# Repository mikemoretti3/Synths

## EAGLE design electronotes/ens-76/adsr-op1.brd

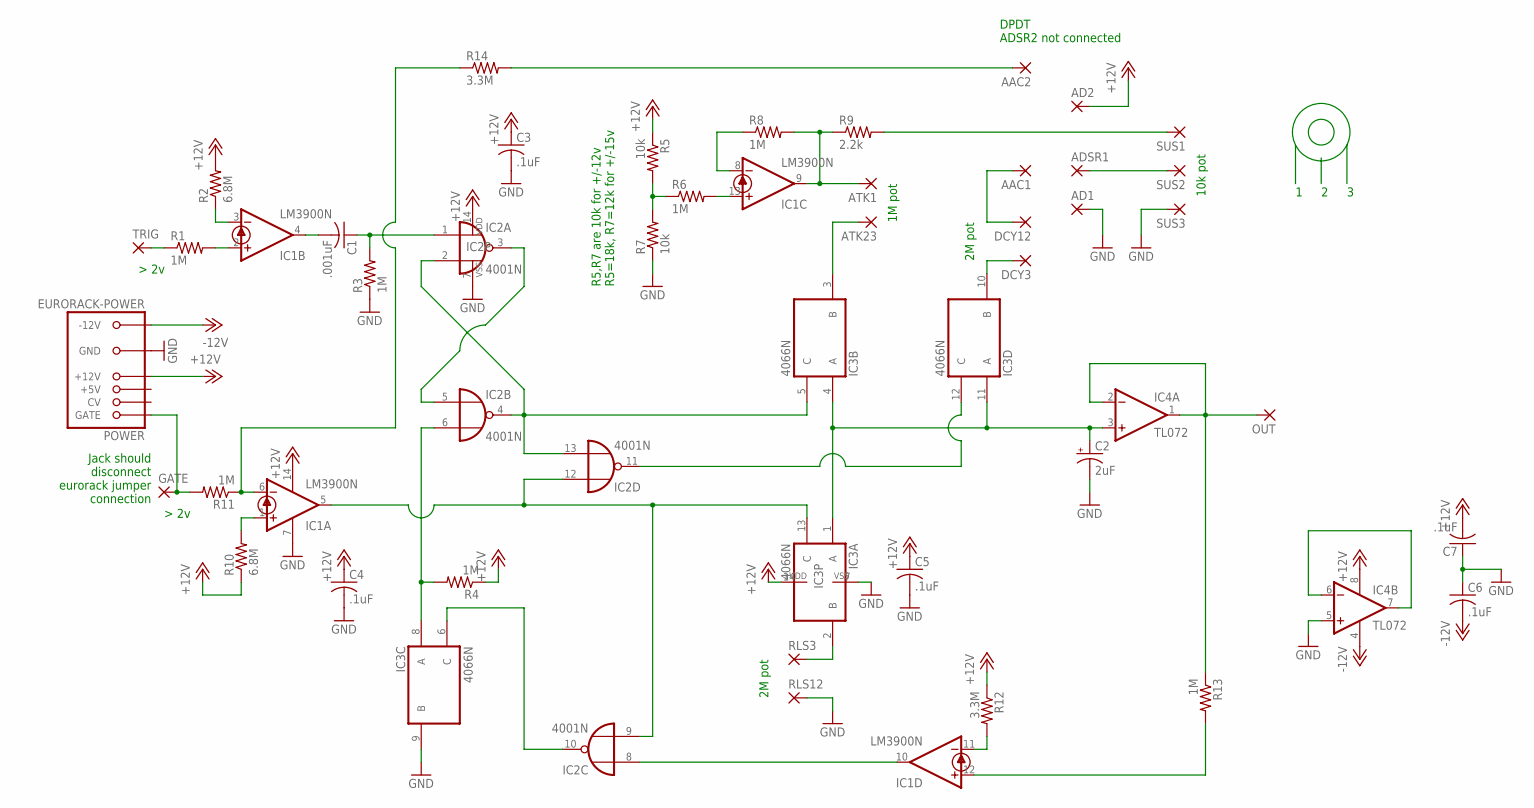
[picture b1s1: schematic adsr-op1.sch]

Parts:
AAC1, AAC2: 2,54/1,0
AD1, AD2: 2,54/1,0
ADSR1: 2,54/1,0
ATK1, ATK23: 2,54/1,0
C1: .001uF; C050-025X075
C2: 2uF; E2,5-5
C3, C4, C5, C6, C7: .1uF; C050-025X075
DCY3, DCY12: 2,54/1,0
GATE: 2,54/1,0
IC1: LM3900N; DIL14
IC2: 4001N; DIL14
IC3: 4066N; DIL14
IC4: TL072; DIL08
OUT: 2,54/1,0
POWER: EURORACK-POWER; PINSHRD_PTH_2X8
R1, R3, R4, R6, R8, R11, R13: 1M; 0207/10
R2, R10: 6.8M; 0207/10
R5, R7: 10k; 0207/10
R9: 2.2k; 0207/10
R12, R14: 3.3M; 0207/10
RLS3, RLS12: 2,54/1,0
SUS1, SUS2, SUS3: 2,54/1,0
TRIG: 2,54/1,0

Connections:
+12V: AD2.1, C3.1, C4.1, C5.1, C7.2, IC1.14 (V+), IC2.14 (VDD), IC3.14 (VDD), IC4.8 (V+), POWER.+12V@1 (+12V), POWER.+12V@2 (+12V), R2.2, R4.1, R5.1, R10.1, R12.1
-12V: C6.2, IC4.4 (V-), POWER.-12V@1 (-12V), POWER.-12V@2 (-12V)
GND: AD1.1, C2.-, C3.2, C4.2, C5.2, C6.1, C7.1, IC1.7 (GND), IC2.7 (VSS), IC3.7 (VSS), IC3.9 (B), IC4.5 (+IN), POWER.GND@1 (GND), POWER.GND@2 (GND), POWER.GND@3 (GND), POWER.GND@4 (GND), POWER.GND@5 (GND), POWER.GND@6 (GND), R3.1, R7.1, RLS12.1, SUS3.1
unnamed: IC4.6 (-IN), IC4.7 (OUT)
unnamed: IC1.3 (-IN), R2.1
unnamed: IC1.2 (+IN), R1.2
unnamed: R1.1, TRIG.1
unnamed: C1.2, IC1.4 (OUT)
unnamed: C1.1, IC2.1 (I0), R3.2
unnamed: IC2.2 (I1), IC2.4 (O), IC2.13 (I1), IC3.5 (C)
unnamed: IC2.3 (O), IC2.5 (I0)
unnamed: IC1.6 (-IN), R11.1, R14.1
unnamed: IC1.1 (+IN), R10.2
unnamed: IC2.10 (O), IC3.6 (C)
unnamed: GATE.1, POWER.GATE@1 (GATE), POWER.GATE@2 (GATE), R11.2
unnamed: IC2.6 (I1), IC3.8 (A), R4.2
unnamed: IC1.5 (OUT), IC2.9 (I1), IC2.12 (I0), IC3.13 (C)
unnamed: IC1.10 (OUT), IC2.8 (I0)
unnamed: IC3.2 (B), RLS3.1
unnamed: IC1.11 (-IN), R12.2
unnamed: C2.+, IC3.1 (A), IC3.4 (A), IC3.11 (A), IC4.3 (+IN)
unnamed: ATK23.1, IC3.3 (B)
unnamed: ATK1.1, IC1.9 (OUT), R8.2, R9.1
unnamed: IC1.13 (+IN), R6.2
unnamed: R5.2, R6.1, R7.2
unnamed: IC1.8 (-IN), R8.1
unnamed: IC2.11 (O), IC3.12 (C)
unnamed: DCY3.1, IC3.10 (B)
unnamed: AAC1.1, DCY12.1
unnamed: ADSR1.1, SUS2.1
unnamed: R9.2, SUS1.1
unnamed: AAC2.1, R14.2
unnamed: IC4.1 (OUT), IC4.2 (-IN), OUT.1, R13.1
unnamed: IC1.12 (+IN), R13.2

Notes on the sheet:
2M pot
1M pot
10k pot
DPDT ADSR2 not connected
R5,R7 are 10k for +/-12v R5=18k, R7=12k for +/-15v
Jack should disconnect eurorack jumper connection

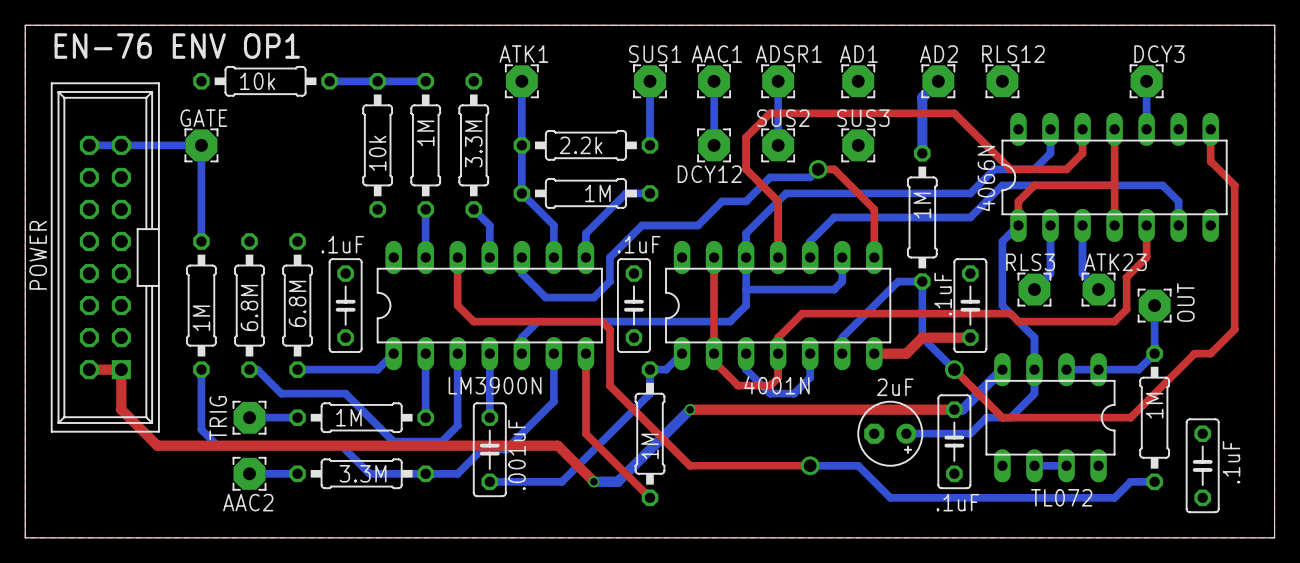
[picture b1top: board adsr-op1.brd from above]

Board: 2 copper layers, 99.1 x 40.6 mm, 43 parts (0 on the bottom side), 34 nets.

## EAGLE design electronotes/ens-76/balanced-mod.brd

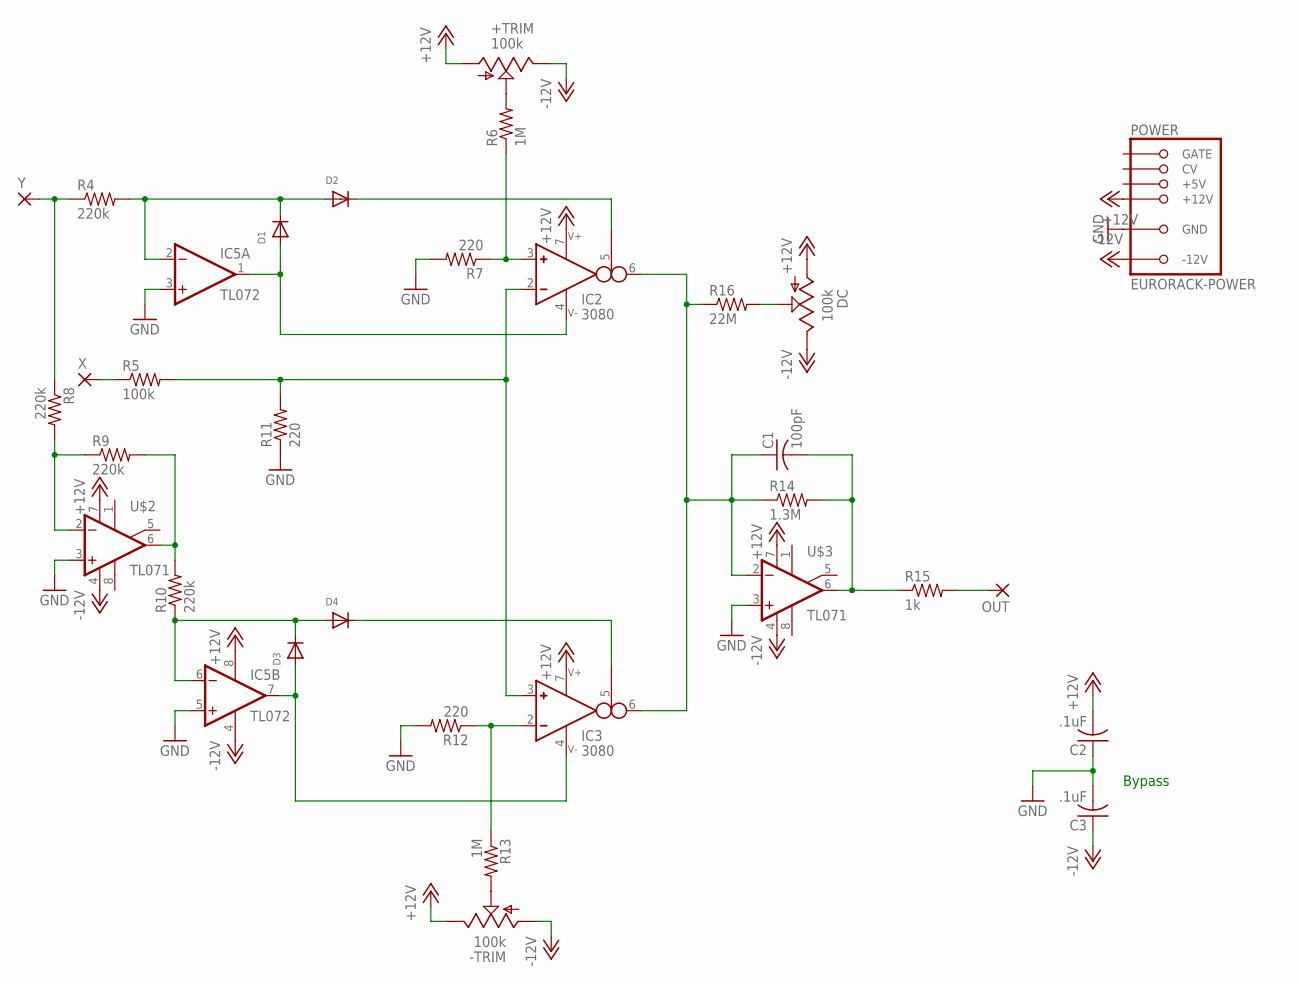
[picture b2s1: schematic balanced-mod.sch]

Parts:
+TRIM: 100k; RJ9W
-TRIM: 100k; RJ9W
C1: 100pF; C050-025X075
C2, C3: .1uF; C050-025X075
D1, D2, D3, D4: DIODEDO-1N4148; DO-1N4148
DC: 100k; RJ9W
IC2, IC3: 3080; DIL08
IC5: TL072; DIL08
OUT: 2,54/1,0
POWER: EURORACK-POWER; PINSHRD_PTH_2X8
R4, R8, R9, R10: 220k; 0207/10
R5: 100k; 0207/10
R6, R13: 1M; 0207/10
R7, R11, R12: 220; 0207/10
R14: 1.3M; 0207/10
R15: 1k; 0207/10
R16: 22M; 0207/10
U$2, U$3: TL071; DIL08
X: 2,54/1,0
Y: 2,54/1,0

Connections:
+12V: +TRIM.A, -TRIM.E, C2.2, DC.A, IC2.7, IC3.7, IC5.8 (V+), POWER.+12V@1 (+12V), POWER.+12V@2 (+12V), U$2.7 (V+), U$3.7 (V+)
-12V: +TRIM.E, -TRIM.A, C3.1, DC.E, IC5.4 (V-), POWER.-12V@1 (-12V), POWER.-12V@2 (-12V), U$2.4 (V-), U$3.4 (V-)
GND: C2.1, C3.2, IC5.3 (+IN), IC5.5 (+IN), POWER.GND@1 (GND), POWER.GND@2 (GND), POWER.GND@3 (GND), POWER.GND@4 (GND), POWER.GND@5 (GND), POWER.GND@6 (GND), R7.2, R11.1, R12.2, U$2.3 (+IN), U$3.3 (+IN)
unnamed: D1.C, D2.A, IC5.2 (-IN), R4.2
unnamed: R4.1, R8.1, Y.1
unnamed: R5.1, X.1
unnamed: +TRIM.S, R6.2
unnamed: IC2.3 (IN_P), R6.1, R7.1
unnamed: D2.C, IC2.5 (I_BIAS)
unnamed: IC2.2 (IN_N), IC3.3 (IN_P), R5.2, R11.2
unnamed: R8.2, R9.1, U$2.2 (-IN)
unnamed: C1.1, IC2.6 (OUT), IC3.6 (OUT), R14.1, R16.1, U$3.2 (-IN)
unnamed: DC.S, R16.2
unnamed: C1.2, R14.2, R15.1, U$3.6 (OUT)
unnamed: OUT.1, R15.2
unnamed: R9.2, R10.2, U$2.6 (OUT)
unnamed: D3.C, D4.A, IC5.6 (-IN), R10.1
unnamed: D3.A, IC3.4, IC5.7 (OUT)
unnamed: D4.C, IC3.5 (I_BIAS)
unnamed: IC3.2 (IN_N), R12.1, R13.1
unnamed: -TRIM.S, R13.2
V-: D1.A, IC2.4, IC5.1 (OUT)

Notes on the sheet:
Bypass

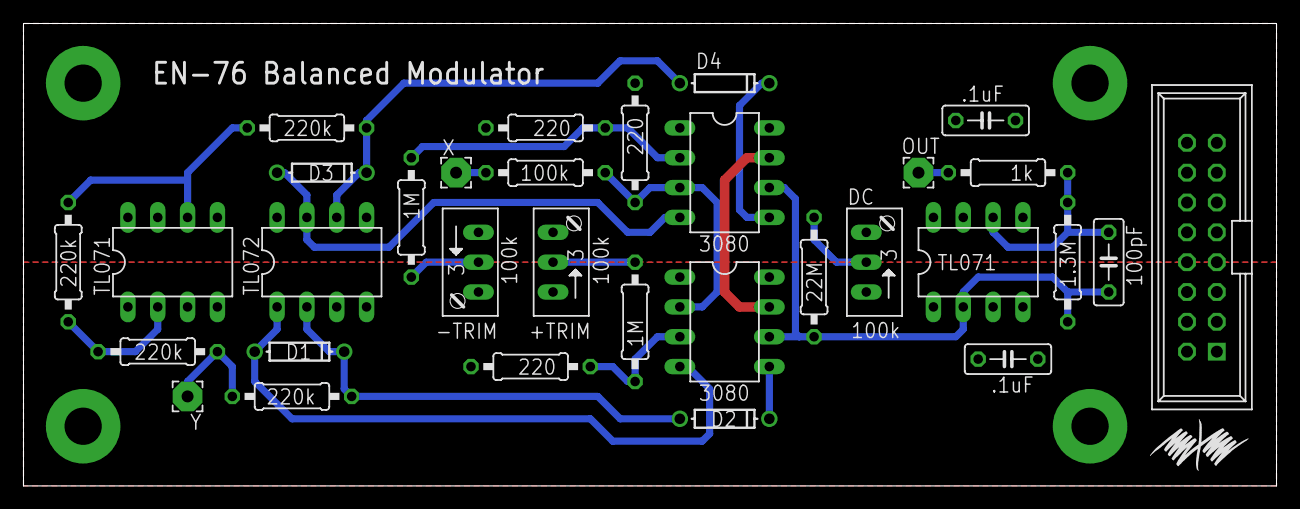
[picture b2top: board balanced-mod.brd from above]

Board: 2 copper layers, 106.7 x 39.4 mm, 32 parts (0 on the bottom side), 22 nets.

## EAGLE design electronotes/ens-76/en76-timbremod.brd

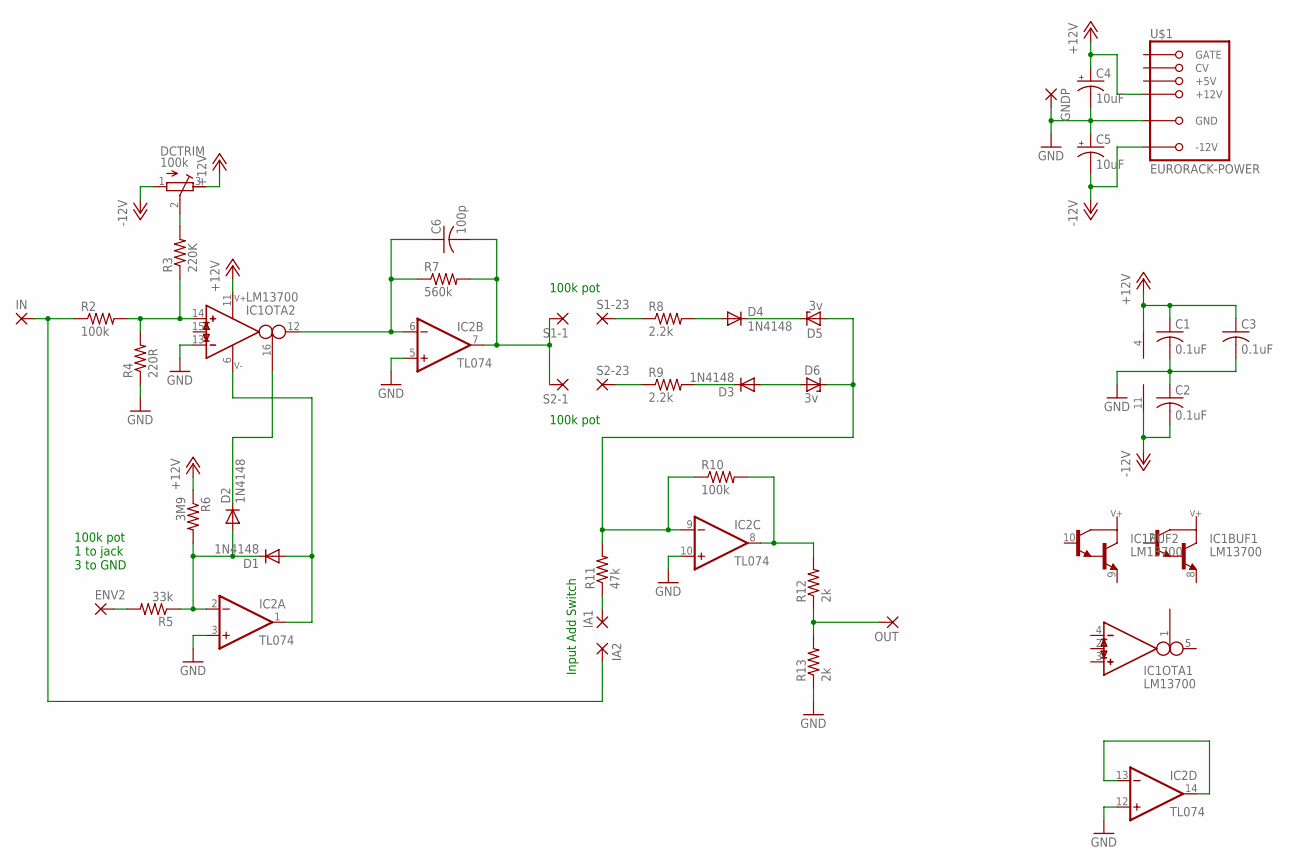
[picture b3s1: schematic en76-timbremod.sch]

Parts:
C1, C2, C3: 0.1uF; C050-025X075
C4, C5: 10uF; E2,5-5
C6: 100p; C050-025X075
D1, D2, D3, D4: 1N4148; DO35-7
D5, D6: 3v; DO35Z10
DCTRIM: 100k; RTRIM64W
ENV2: 2,54/1,0
GNDP: 2,54/1,0
IA1, IA2: 2,54/1,0
IC1: LM13700; DIL16
IC2: TL074; DIL14
IN: 2,54/1,0
OUT: 2,54/1,0
R2, R10: 100k; 0207/10
R3: 220K; 0207/10
R4: 220R; 0207/10
R5: 33k; 0207/10
R6: 3M9; 0207/10
R7: 560k; 0207/10
R8, R9: 2.2k; 0207/10
R11: 47k; 0207/10
R12, R13: 2k; 0207/10
S1-1, S1-23, S2-1, S2-23: 2,54/1,0
U$1: EURORACK-POWER; PINSHRD_PTH_2X8

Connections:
+12V: C1.1, C3.1, C4.+, DCTRIM.3 (E), IC1.11 (7), IC2.4 (V+), R6.1, U$1.+12V@1 (+12V), U$1.+12V@2 (+12V)
-12V: C2.2, C5.-, DCTRIM.1 (A), IC2.11 (V-), U$1.-12V@1 (-12V), U$1.-12V@2 (-12V)
GND: C1.2, C2.1, C3.2, C4.-, C5.+, GNDP.1, IC1.13 (IN_N), IC2.3 (+IN), IC2.5 (+IN), IC2.10 (+IN), IC2.12 (+IN), R4.1, R13.1, U$1.GND@1 (GND), U$1.GND@2 (GND), U$1.GND@3 (GND), U$1.GND@4 (GND), U$1.GND@5 (GND), U$1.GND@6 (GND)
unnamed: IA2.1, IN.1, R2.1
unnamed: IC1.14 (IN_P), R2.2, R3.1, R4.2
unnamed: DCTRIM.2 (S), R3.2
unnamed: ENV2.1, R5.2
unnamed: D1.C, D2.A, IC2.2 (-IN), R5.1, R6.2
unnamed: D1.A, IC1.6 (4), IC2.1 (OUT)
unnamed: D2.C, IC1.16 (I_BIAS)
unnamed: C6.1, IC1.12 (OUT), IC2.6 (-IN), R7.1
unnamed: C6.2, IC2.7 (OUT), R7.2, S1-1.1, S2-1.1
unnamed: D4.A, R8.2
unnamed: D3.C, R9.2
unnamed: D4.C, D5.C
unnamed: D3.A, D6.A
unnamed: R8.1, S1-23.1
unnamed: D5.A, D6.C, IC2.9 (-IN), R10.1, R11.2
unnamed: R9.1, S2-23.1
unnamed: IA1.1, R11.1
unnamed: IC2.8 (OUT), R10.2, R12.2
unnamed: OUT.1, R12.1, R13.2
unnamed: IC2.13 (-IN), IC2.14 (OUT)

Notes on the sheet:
100k pot 1 to jack 3 to GND
100k pot
Input Add Switch

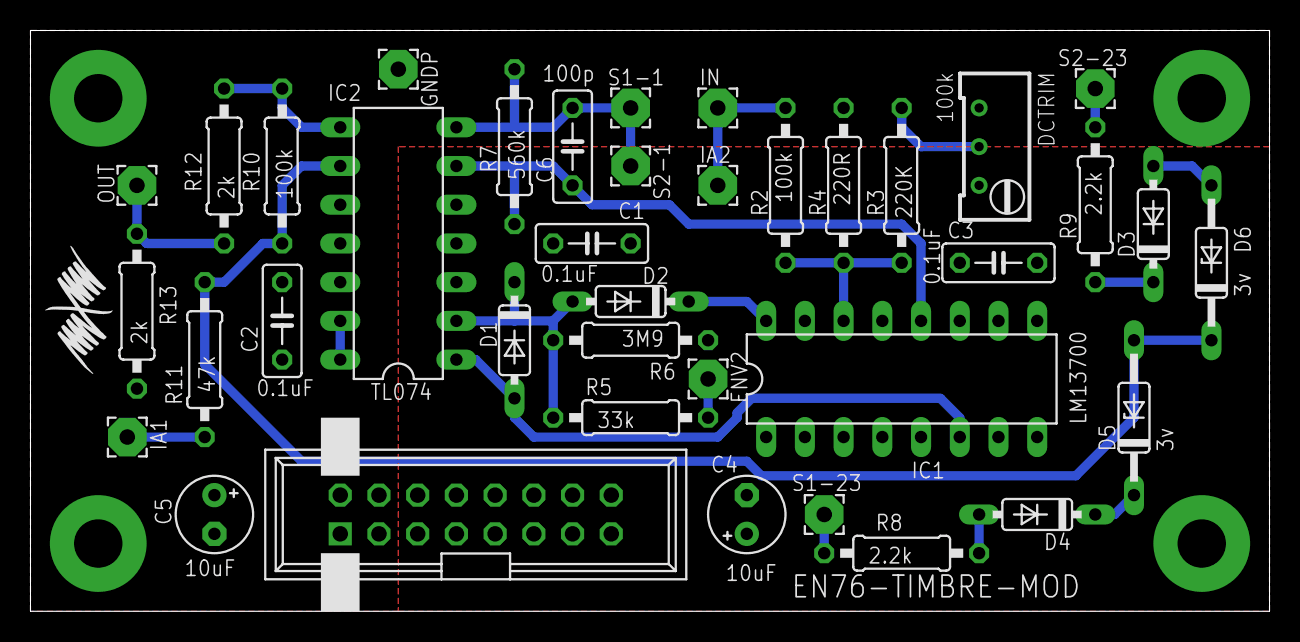
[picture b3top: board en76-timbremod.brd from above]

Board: 2 copper layers, 81.3 x 38.1 mm, 38 parts (0 on the bottom side), 23 nets.

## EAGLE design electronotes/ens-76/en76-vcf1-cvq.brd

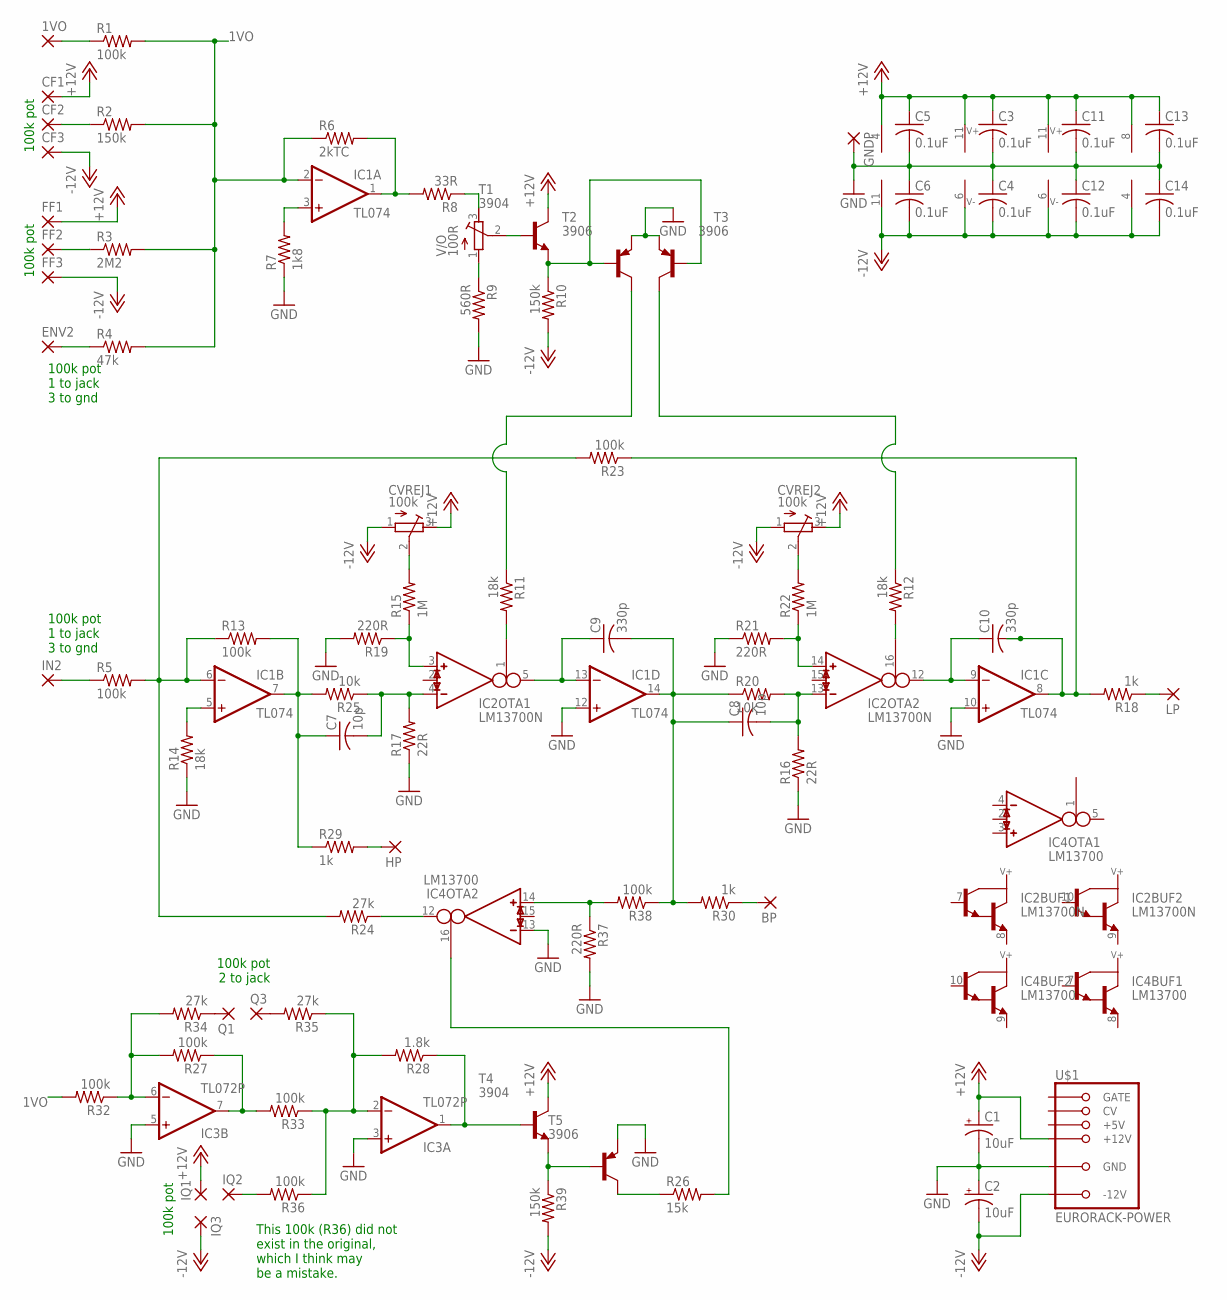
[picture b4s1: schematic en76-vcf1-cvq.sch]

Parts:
1VO: 2,54/1,0
BP: 2,54/1,0
C1, C2: 10uF; E2,5-5
C3, C4, C5, C6, C11, C12, C13, C14: 0.1uF; C050-025X075
C7, C8: 10p; C050-025X075
C9, C10: 330p; C050-025X075
CF1, CF2, CF3: 2,54/1,0
CVREJ1, CVREJ2: 100k; RTRIM64W
ENV2: 2,54/1,0
FF1, FF2, FF3: 2,54/1,0
GNDP: 2,54/1,0
HP: 2,54/1,0
IC1: TL074; DIL14
IC2: LM13700N; DIL16
IC3: TL072P; DIL08
IC4: LM13700; DIL16
IN2: 2,54/1,0
IQ1, IQ2, IQ3: 2,54/1,0
LP: 2,54/1,0
Q1, Q3: 2,54/1,0
R1, R5, R13, R23, R27, R32, R33, R36, R38: 100k; 0207/10
R2, R10, R39: 150k; 0207/10
R3: 2M2; 0207/10
R4: 47k; 0207/10
R6: 2kTC; 0207/10
R7: 1k8; 0207/10
R8: 33R; 0207/10
R9: 560R; 0207/10
R11, R12, R14: 18k; 0207/10
R15, R22: 1M; 0207/10
R16, R17: 22R; 0207/10
R18, R29, R30: 1k; 0207/10
R19, R21, R37: 220R; 0207/10
R20, R25: 10k; 0207/10
R24, R34, R35: 27k; 0207/10
R26: 15k; 0207/10
R28: 1.8k; 0207/10
T1, T4: 3904; TO92-EBC
T2, T3, T5: 3906; TO92-EBC
U$1: EURORACK-POWER; PINSHRD_PTH_2X8
V/O: 100R; RTRIM64W

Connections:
1VO: IC1.2 (-IN), R1.2, R2.2, R3.2, R4.2, R6.1, R32.2
+12V: C1.+, C3.1, C5.1, C11.1, C13.1, CF1.1, CVREJ1.3 (E), CVREJ2.3 (E), FF1.1, IC1.4 (V+), IC2.11 (7), IC3.8 (V+), IC4.11 (7), IQ1.1, T1.C, T4.C, U$1.+12V@1 (+12V), U$1.+12V@2 (+12V)
-12V: C2.-, C4.2, C6.2, C12.2, C14.2, CF3.1, CVREJ1.1 (A), CVREJ2.1 (A), FF3.1, IC1.11 (V-), IC2.6 (4), IC3.4 (V-), IC4.6 (4), IQ3.1, R10.2, R39.2, U$1.-12V@1 (-12V), U$1.-12V@2 (-12V)
GND: C1.-, C2.+, C3.2, C4.1, C5.2, C6.1, C11.2, C12.1, C13.2, C14.1, GNDP.1, IC1.10 (+IN), IC1.12 (+IN), IC3.3 (+IN), IC3.5 (+IN), IC4.13 (IN_N), R7.1, R9.2, R14.1, R16.1, R17.1, R19.2, R21.1, R37.2, T2.E, T3.E, T5.E, U$1.GND@1 (GND), U$1.GND@2 (GND), U$1.GND@3 (GND), U$1.GND@4 (GND), U$1.GND@5 (GND), U$1.GND@6 (GND)
unnamed: 1VO.1, R1.1
unnamed: CF2.1, R2.1
unnamed: FF2.1, R3.1
unnamed: ENV2.1, R4.1
unnamed: IN2.1, R5.1
unnamed: IC1.6 (-IN), R5.2, R13.1, R23.2, R24.2
unnamed: C7.1, IC1.7 (OUT), R13.2, R25.2, R29.1
unnamed: IC1.5 (+IN), R14.2
unnamed: C9.1, IC1.13 (-IN), IC2.5 (OUT)
unnamed: C8.1, C9.2, IC1.14 (OUT), R20.1, R30.2, R38.1
unnamed: C10.1, IC1.9 (-IN), IC2.12 (OUT)
unnamed: C10.2, IC1.8 (OUT), R18.2, R23.1
unnamed: IC2.14 (IN_P), R21.2, R22.1
unnamed: CVREJ2.2 (S), R22.2
unnamed: C8.2, IC2.13 (IN_N), R16.2, R20.2
unnamed: IC3.7 (OUT), R27.1, R33.2
unnamed: IC1.1 (OUT), R6.2, R8.2
unnamed: IC1.3 (+IN), R7.2
unnamed: C7.2, IC2.4 (IN_N), R17.2, R25.1
unnamed: R9.1, V/O.1 (A)
unnamed: R8.1, V/O.3 (E)
unnamed: T1.B, V/O.2 (S)
unnamed: R10.1, T1.E, T2.B, T3.B
unnamed: IC2.3 (IN_P), R15.1, R19.1
unnamed: CVREJ1.2 (S), R15.2
unnamed: IC2.1 (I_BIAS), R11.2
unnamed: HP.1, R29.2
unnamed: IC2.16 (I_BIAS), R12.2
unnamed: LP.1, R18.1
unnamed: BP.1, R30.1
unnamed: IQ2.1, R36.2
unnamed: Q1.1, R34.1
unnamed: R12.1, T3.C
unnamed: R11.1, T2.C
unnamed: IC4.12 (OUT), R24.1
unnamed: R26.1, T5.C
unnamed: R39.1, T4.E, T5.B
unnamed: IC3.2 (-IN), R28.2, R33.1, R35.1, R36.1
unnamed: IC3.6 (-IN), R27.2, R32.1, R34.2
unnamed: IC3.1 (OUT), R28.1, T4.B
unnamed: Q3.1, R35.2
unnamed: IC4.14 (IN_P), R37.1, R38.2
unnamed: IC4.16 (I_BIAS), R26.2

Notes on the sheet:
100k pot 1 to jack 3 to gnd
100k pot
100k pot 2 to jack
This 100k (R36) did not exist in the original, which I think may be a mistake.

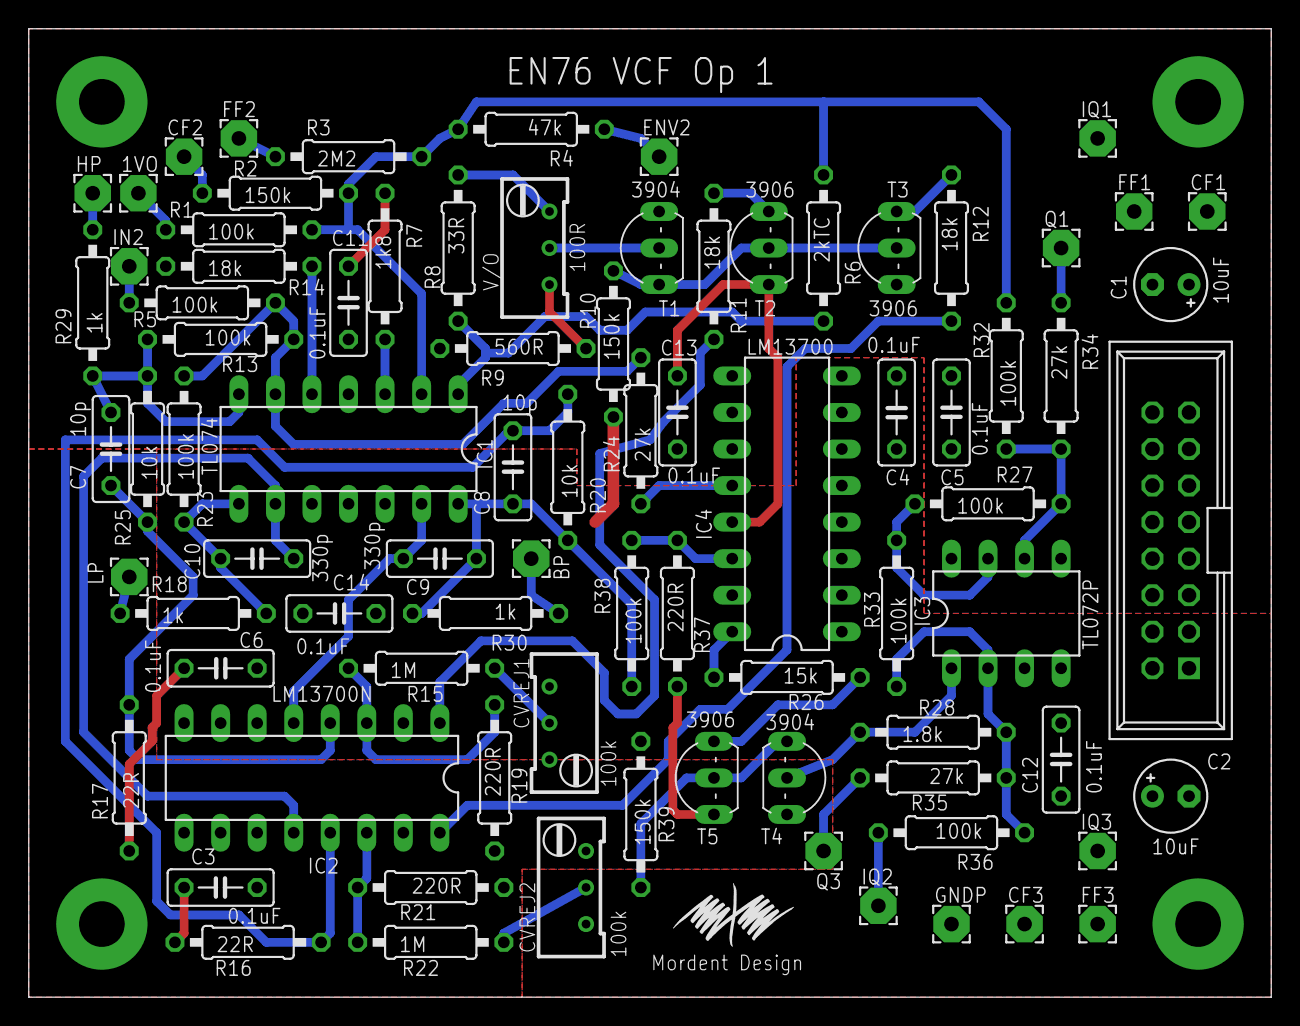
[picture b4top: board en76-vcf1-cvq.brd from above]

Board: 2 copper layers, 86.4 x 67.3 mm, 83 parts (0 on the bottom side), 47 nets.

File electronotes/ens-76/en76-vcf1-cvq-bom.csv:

"Part";"Value";"Device";"Package";"Description";"";
"1VO";"";"2,54/1,0";"2,54/1,0";"THROUGH-HOLE PAD";"";
"BP";"";"2,54/1,0";"2,54/1,0";"THROUGH-HOLE PAD";"";
"C1";"10uF";"CPOL-USE2.5-5";"E2,5-5";"POLARIZED CAPACITOR, American symbol";"";
"C2";"10uF";"CPOL-USE2.5-5";"E2,5-5";"POLARIZED CAPACITOR, American symbol";"";
"C3";"0.1uF";"C-US050-025X075";"C050-025X075";"CAPACITOR, American symbol";"";
"C4";"0.1uF";"C-US050-025X075";"C050-025X075";"CAPACITOR, American symbol";"";
"C5";"0.1uF";"C-US050-025X075";"C050-025X075";"CAPACITOR, American symbol";"";
"C6";"0.1uF";"C-US050-025X075";"C050-025X075";"CAPACITOR, American symbol";"";
"C7";"10p";"C-US050-025X075";"C050-025X075";"CAPACITOR, American symbol";"";
"C8";"10p";"C-US050-025X075";"C050-025X075";"CAPACITOR, American symbol";"";
"C9";"330p";"C-US050-025X075";"C050-025X075";"CAPACITOR, American symbol";"";
"C10";"330p";"C-US050-025X075";"C050-025X075";"CAPACITOR, American symbol";"";
"C11";"0.1uF";"C-US050-025X075";"C050-025X075";"CAPACITOR, American symbol";"";
"C12";"0.1uF";"C-US050-025X075";"C050-025X075";"CAPACITOR, American symbol";"";
"C13";"0.1uF";"C-US050-025X075";"C050-025X075";"CAPACITOR, American symbol";"";
"C14";"0.1uF";"C-US050-025X075";"C050-025X075";"CAPACITOR, American symbol";"";
"CF1";"";"2,54/1,0";"2,54/1,0";"THROUGH-HOLE PAD";"";
"CF2";"";"2,54/1,0";"2,54/1,0";"THROUGH-HOLE PAD";"";
"CF3";"";"2,54/1,0";"2,54/1,0";"THROUGH-HOLE PAD";"";
"CVREJ1";"100k";"R-TRIMM64W";"RTRIM64W";"Trimm resistor";"";
"CVREJ2";"100k";"R-TRIMM64W";"RTRIM64W";"Trimm resistor";"";
"ENV2";"";"2,54/1,0";"2,54/1,0";"THROUGH-HOLE PAD";"";
"FF1";"";"2,54/1,0";"2,54/1,0";"THROUGH-HOLE PAD";"";
"FF2";"";"2,54/1,0";"2,54/1,0";"THROUGH-HOLE PAD";"";
"FF3";"";"2,54/1,0";"2,54/1,0";"THROUGH-HOLE PAD";"";
"GNDP";"";"2,54/1,0";"2,54/1,0";"THROUGH-HOLE PAD";"";
"HP";"";"2,54/1,0";"2,54/1,0";"THROUGH-HOLE PAD";"";
"IC1";"TL074";"TL074-TOPP";"DIL14";"OP AMP";"";
"IC2";"LM13700N";"LM13700N";"DIL16";"Dual OTA with buffers";"";
"IC3";"TL072P";"TL072P";"DIL08";"OP AMP";"";
"IC4";"LM13700";"LM13700-TOPDIP16";"DIL16";"";"";
"IN2";"";"2,54/1,0";"2,54/1,0";"THROUGH-HOLE PAD";"";
"IQ1";"";"2,54/1,0";"2,54/1,0";"THROUGH-HOLE PAD";"";
"IQ2";"";"2,54/1,0";"2,54/1,0";"THROUGH-HOLE PAD";"";
"IQ3";"";"2,54/1,0";"2,54/1,0";"THROUGH-HOLE PAD";"";
"LP";"";"2,54/1,0";"2,54/1,0";"THROUGH-HOLE PAD";"";
"Q1";"";"2,54/1,0";"2,54/1,0";"THROUGH-HOLE PAD";"";
"Q3";"";"2,54/1,0";"2,54/1,0";"THROUGH-HOLE PAD";"";
"R1";"100k";"R-US_0207/10";"0207/10";"RESISTOR, American symbol";"";
"R2";"150k";"R-US_0207/10";"0207/10";"RESISTOR, American symbol";"";
"R3";"2M2";"R-US_0207/10";"0207/10";"RESISTOR, American symbol";"";
"R4";"47k";"R-US_0207/10";"0207/10";"RESISTOR, American symbol";"";
"R5";"100k";"R-US_0207/10";"0207/10";"RESISTOR, American symbol";"";
"R6";"2kTC";"R-US_0207/10";"0207/10";"RESISTOR, American symbol";"";
"R7";"1k8";"R-US_0207/10";"0207/10";"RESISTOR, American symbol";"";
"R8";"33R";"R-US_0207/10";"0207/10";"RESISTOR, American symbol";"";
"R9";"560R";"R-US_0207/10";"0207/10";"RESISTOR, American symbol";"";
"R10";"150k";"R-US_0207/10";"0207/10";"RESISTOR, American symbol";"";
"R11";"18k";"R-US_0207/10";"0207/10";"RESISTOR, American symbol";"";
"R12";"18k";"R-US_0207/10";"0207/10";"RESISTOR, American symbol";"";
"R13";"100k";"R-US_0207/10";"0207/10";"RESISTOR, American symbol";"";
"R14";"18k";"R-US_0207/10";"0207/10";"RESISTOR, American symbol";"";
"R15";"1M";"R-US_0207/10";"0207/10";"RESISTOR, American symbol";"";
"R16";"22R";"R-US_0207/10";"0207/10";"RESISTOR, American symbol";"";
"R17";"22R";"R-US_0207/10";"0207/10";"RESISTOR, American symbol";"";
"R18";"1k";"R-US_0207/10";"0207/10";"RESISTOR, American symbol";"";
"R19";"220R";"R-US_0207/10";"0207/10";"RESISTOR, American symbol";"";
"R20";"10k";"R-US_0207/10";"0207/10";"RESISTOR, American symbol";"";
"R21";"220R";"R-US_0207/10";"0207/10";"RESISTOR, American symbol";"";
"R22";"1M";"R-US_0207/10";"0207/10";"RESISTOR, American symbol";"";
"R23";"100k";"R-US_0207/10";"0207/10";"RESISTOR, American symbol";"";
"R24";"27k";"R-US_0207/10";"0207/10";"RESISTOR, American symbol";"";
"R25";"10k";"R-US_0207/10";"0207/10";"RESISTOR, American symbol";"";
"R26";"15k";"R-US_0207/10";"0207/10";"RESISTOR, American symbol";"";
"R27";"100k";"R-US_0207/10";"0207/10";"RESISTOR, American symbol";"";
"R28";"1.8k";"R-US_0207/10";"0207/10";"RESISTOR, American symbol";"";
"R29";"1k";"R-US_0207/10";"0207/10";"RESISTOR, American symbol";"";
"R30";"1k";"R-US_0207/10";"0207/10";"RESISTOR, American symbol";"";
"R32";"100k";"R-US_0207/10";"0207/10";"RESISTOR, American symbol";"";
"R33";"100k";"R-US_0207/10";"0207/10";"RESISTOR, American symbol";"";
"R34";"27k";"R-US_0207/10";"0207/10";"RESISTOR, American symbol";"";
"R35";"27k";"R-US_0207/10";"0207/10";"RESISTOR, American symbol";"";
"R36";"100k";"R-US_0207/10";"0207/10";"RESISTOR, American symbol";"";
"R37";"220R";"R-US_0207/10";"0207/10";"RESISTOR, American symbol";"";
"R38";"100k";"R-US_0207/10";"0207/10";"RESISTOR, American symbol";"";
"R39";"150k";"R-US_0207/10";"0207/10";"RESISTOR, American symbol";"";
"T1";"3904";"-NPN-TO92-EBC";"TO92-EBC";"NPN Transistror";"";
"T2";"3906";"-PNP-TO92-EBC";"TO92-EBC";"PNP Transistror";"";
"T3";"3906";"-PNP-TO92-EBC";"TO92-EBC";"PNP Transistror";"";
"T4";"3904";"-NPN-TO92-EBC";"TO92-EBC";"NPN Transistror";"";
"T5";"3906";"-PNP-TO92-EBC";"TO92-EBC";"PNP Transistror";"";
"U$1";"EURORACK-POWER";"EURORACK-POWER";"PINSHRD_PTH_2X8";"";"";
"V/O";"100R";"R-TRIMM64W";"RTRIM64W";"Trimm resistor";"";

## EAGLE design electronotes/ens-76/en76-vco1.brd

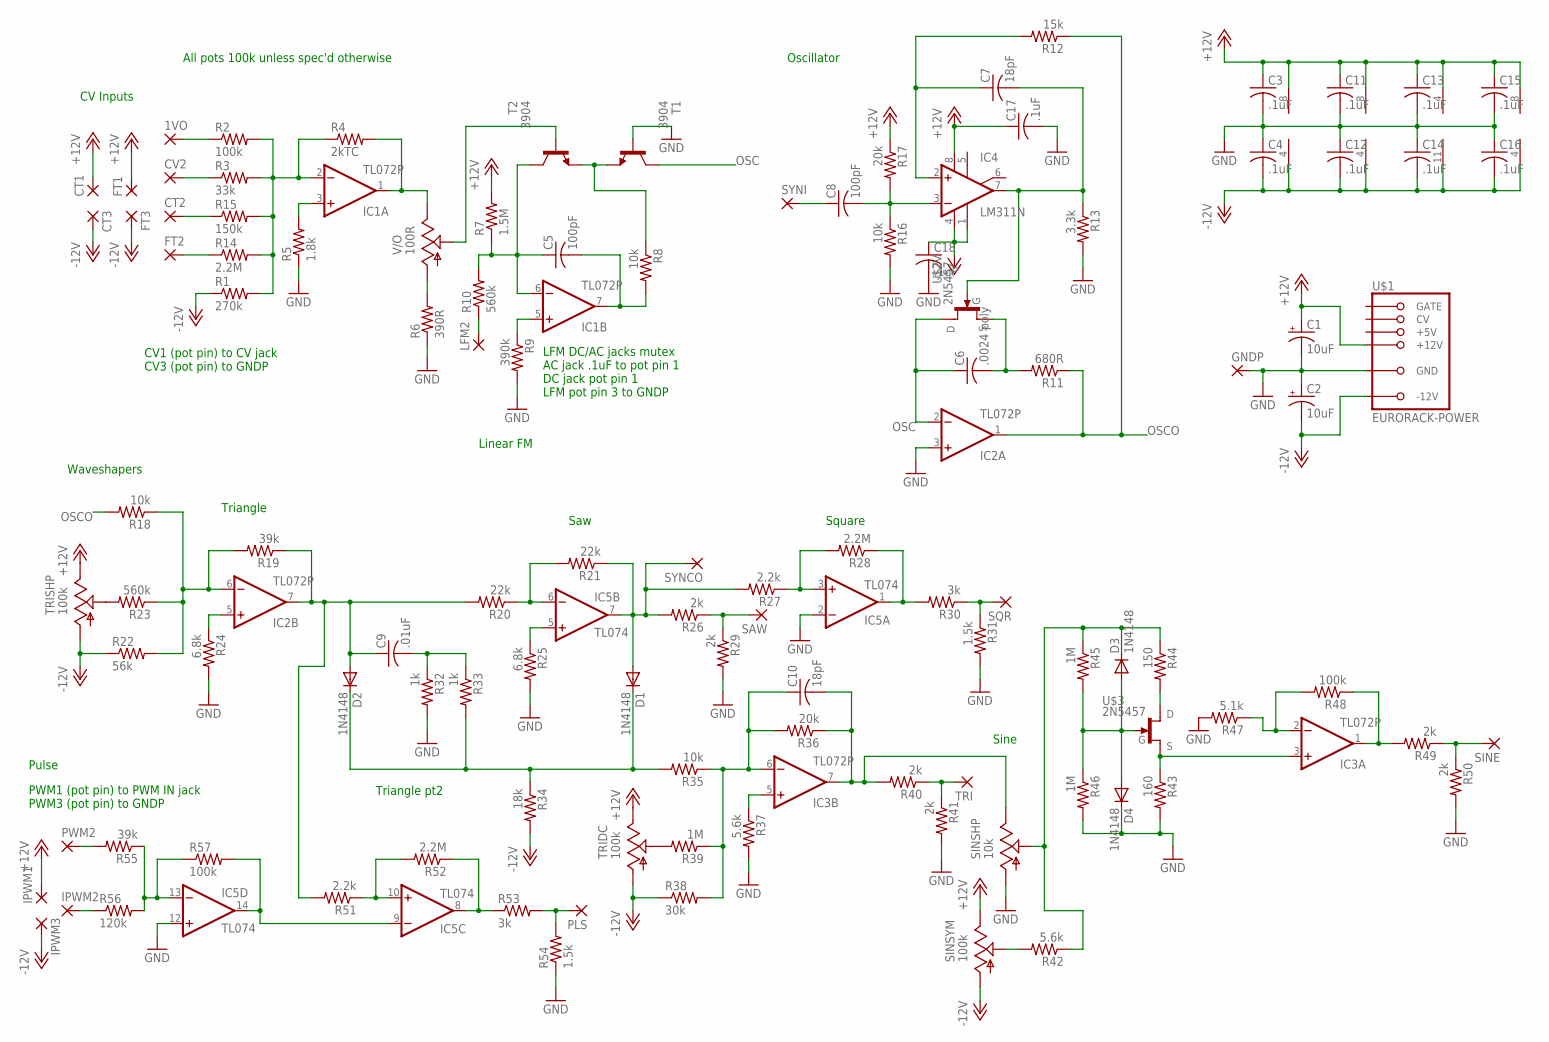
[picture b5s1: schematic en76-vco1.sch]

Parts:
1VO: 2,54/1,0
C1, C2: 10uF; E2-5
C3, C4, C11, C12, C13, C14, C15, C16, C17, C18: .1uF; C050-025X075
C5, C8: 100pF; C050-025X075
C6: .0024 poly; C050-025X075
C7, C10: 18pF; C050-025X075
C9: .01uF; C050-025X075
CT1, CT2, CT3: 2,54/1,0
CV2: 2,54/1,0
D1, D2, D3, D4: 1N4148; DO35-7
FT1, FT2, FT3: 2,54/1,0
GNDP: 2,54/1,0
IC1, IC2, IC3: TL072P; DIL08
IC4: LM311N; DIL08
IC5: TL074; DIL14
IPWM1, IPWM2, IPWM3: 2,54/1,0
LFM2: 2,54/1,0
PLS: 2,54/1,0
PWM2: 2,54/1,0
R1: 270k; 0207/10
R2, R48, R57: 100k; 0207/10
R3: 33k; 0207/10
R4: 2kTC; 0207/10
R5: 1.8k; 0207/10
R6: 390R; 0207/10
R7: 1.5M; 0207/10
R8, R16, R18, R35: 10k; 0207/10
R9: 390k; 0207/10
R10, R23: 560k; 0207/10
R11: 680R; 0207/10
R12: 15k; 0207/10
R13: 3.3k; 0207/10
R14, R28, R52: 2.2M; 0207/10
R15: 150k; 0207/10
R17, R36: 20k; 0207/10
R19, R55: 39k; 0207/10
R20, R21: 22k; 0207/10
R22: 56k; 0207/10
R24, R25: 6.8k; 0207/10
R26, R29, R40, R41, R49, R50: 2k; 0207/10
R27, R51: 2.2k; 0207/10
R30, R53: 3k; 0207/10
R31, R54: 1.5k; 0207/10
R32, R33: 1k; 0207/10
R34: 18k; 0207/10
R37, R42: 5.6k; 0207/10
R38: 30k; 0207/10
R39, R45, R46: 1M; 0207/10
R43: 160; 0207/10
R44: 150; 0207/10
R47: 5.1k; 0207/10
R56: 120k; 0207/10
SAW: 2,54/1,0
SINE: 2,54/1,0
SINSHP: 10k; RJ9W
SINSYM: 100k; RJ9W
SQR: 2,54/1,0
SYNCO: 2,54/1,0
SYNI: 2,54/1,0
T1, T2: 3904; TO92-EBC
TRI: 2,54/1,0
TRIDC: 100k; RJ9W
TRISHP: 100k; RJ9W
U$1: EURORACK-POWER; PINSHRD_PTH_2X8
U$2, U$3: 2N5457; TO-92
V/O: 100R; RJ9W

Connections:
+12V: C1.+, C3.1, C11.1, C13.1, C15.1, C17.1, CT1.1, FT1.1, IC1.8 (V+), IC2.8 (V+), IC3.8 (V+), IC4.8 (V+), IC5.4 (V+), IPWM1.1, R7.2, R17.1, SINSYM.E, TRIDC.E, TRISHP.E, U$1.+12V@1 (+12V), U$1.+12V@2 (+12V)
-12V: C2.-, C4.2, C12.2, C14.2, C16.2, C18.1, CT3.1, FT3.1, IC1.4 (V-), IC2.4 (V-), IC3.4 (V-), IC4.1 (GND), IC4.4 (V-), IC5.11 (V-), IPWM3.1, R1.1, R22.1, R34.2, R38.1, SINSYM.A, TRIDC.A, TRISHP.A, U$1.-12V@1 (-12V), U$1.-12V@2 (-12V)
GND: C1.-, C2.+, C3.2, C4.1, C11.2, C12.1, C13.2, C14.1, C15.2, C16.1, C17.2, C18.2, D4.C, GNDP.1, IC2.3 (+IN), IC5.2 (-IN), IC5.12 (+IN), R5.1, R6.1, R9.2, R13.2, R16.2, R24.2, R25.2, R29.2, R31.2, R32.2, R37.2, R41.2, R43.2, R46.2, R47.2, R50.2, R54.1, SINSHP.A, T1.B, U$1.GND@1 (GND), U$1.GND@2 (GND), U$1.GND@3 (GND), U$1.GND@4 (GND), U$1.GND@5 (GND), U$1.GND@6 (GND)
unnamed: CT2.1, R15.1
unnamed: CV2.1, R3.1
unnamed: 1VO.1, R2.1
unnamed: T2.B, V/O.S
unnamed: IC1.3 (+IN), R5.2
unnamed: IC1.2 (-IN), R1.2, R2.2, R3.2, R4.1, R14.2, R15.2
unnamed: IC1.1 (OUT), R4.2, V/O.E
unnamed: R6.2, V/O.A
unnamed: C5.1, IC1.6 (-IN), R7.1, R10.2, T2.C
unnamed: R8.1, T1.E, T2.E
unnamed: C5.2, IC1.7 (OUT), R8.2
unnamed: FT2.1, R14.1
unnamed: LFM2.1, R10.1
unnamed: IC1.5 (+IN), R9.1
unnamed: C7.1, IC4.2 (+IN), R12.2
unnamed: C7.2, IC4.7 (OUT), R13.1, U$2.3 (G)
unnamed: R23.2, TRISHP.S
unnamed: C6.2, R11.2, U$2.2 (S)
unnamed: D1.A, IC5.7 (OUT), R21.1, R26.2, R27.2, SYNCO.1
unnamed: C8.1, SYNI.1
unnamed: C8.2, IC4.3 (-IN), R16.1, R17.2
unnamed: PWM2.1, R55.2
unnamed: IC2.5 (+IN), R24.1
unnamed: IC2.6 (-IN), R18.1, R19.2, R22.2, R23.1
unnamed: R26.1, R29.1, SAW.1
unnamed: IC5.6 (-IN), R20.1, R21.2
unnamed: C9.2, R32.1, R33.1
unnamed: IC5.5 (+IN), R25.1
unnamed: IC5.3 (+IN), R27.1, R28.2
unnamed: IC5.1 (OUT), R28.1, R30.2
unnamed: R30.1, R31.1, SQR.1
unnamed: D1.C, D2.C, R33.2, R34.1, R35.2
unnamed: R40.1, R41.1, TRI.1
unnamed: C10.2, IC3.7 (OUT), R36.1, R40.2, SINSHP.E
unnamed: IC3.5 (+IN), R37.1
unnamed: R39.2, TRIDC.S
unnamed: C10.1, IC3.6 (-IN), R35.1, R36.2, R38.2, R39.1
unnamed: IC3.3 (+IN), R43.1, U$3.2 (S)
unnamed: R44.2, U$3.1 (D)
unnamed: D3.A, D4.A, R45.2, R46.1, U$3.3 (G)
unnamed: R42.2, SINSYM.S
unnamed: D3.C, R42.1, R44.1, R45.1, SINSHP.S
unnamed: IC3.2 (-IN), R47.1, R48.2
unnamed: R49.1, R50.1, SINE.1
unnamed: IC3.1 (OUT), R48.1, R49.2
unnamed: IC5.9 (-IN), IC5.14 (OUT), R57.2
unnamed: IC5.10 (+IN), R51.1, R52.2
unnamed: IC5.8 (OUT), R52.1, R53.1
unnamed: PLS.1, R53.2, R54.2
unnamed: C9.1, D2.A, IC2.7 (OUT), R19.1, R20.2, R51.2
unnamed: IPWM2.1, R56.1
unnamed: IC5.13 (-IN), R55.1, R56.2, R57.1
OSC: C6.1, IC2.2 (-IN), T1.C, U$2.1 (D)
OSCO: IC2.1 (OUT), R11.1, R12.1, R18.2

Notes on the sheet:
CV1 (pot pin) to CV jack CV3 (pot pin) to GNDP
LFM DC/AC jacks mutex AC jack .1uF to pot pin 1 DC jack pot pin 1 LFM pot pin 3 to GNDP
All pots 100k unless spec'd otherwise
PWM1 (pot pin) to PWM IN jack PWM3 (pot pin) to GNDP
CV Inputs
Oscillator
Waveshapers
Triangle
Saw
Square
Triangle pt2
Sine
Pulse
Linear FM

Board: 2 copper layers, 115 parts (0 on the bottom side), 57 nets, no tracks yet.
